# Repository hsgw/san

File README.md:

SAN 
=======================================

3keys macro pad.
- STM32F042F6P6
- kailh hotswap socket (MX compatible switch)
- on-chip usb-DFU bootloader
- QMK Firmware(https://github.com/hsgw/qmk_firmware/tree/san)

## Issues
### Rev.1
- 基板上の`BOOT`と`RESET`のシルクが逆になっている
(正しくは`SW1 RESET`, `SW2 BOOT`)

## ビルドガイド
1. 組立てる前にPCと接続してキーボードとして認識されるか、動作を確認する
(ファームウェアが書かれていない場合はブートローダモードで接続されます)
2. ブートローダへ入ってQMK Firmwareからの書き込みを確認する
https://github.com/hsgw/qmk_firmware/san
3. プレート、スイッチを取り付ける
4. ボトムプレートを取り付ける

## ブートローダモード
### 入り方
1. RESETスイッチを押す
2. BOOTスイッチを押す
3. RESETスイッチを離す
4. BOOTスイッチを離す

### (windowsの場合)ドライバを入れ替える
Zadigを使用してOS標準で入るドライバをWinUSBのものに入れ替える必要があります。
1. zadigをダウンロード、解凍する。(https://zadig.akeo.ie/)
2. キーボードをbootloaderモードでPCに接続する   
(この段階では```STM Device in DFU Mode```として認識されているはず)
3. zadigを起動して```Options → List All devices```にチェック
4. ```STM Device in DFU Mode```もしくは```STM32 BOOTLOADER```を選択して、```WinUSB```をインストールする   
**書き換えるデバイス名を必ず確認してから```Replace Driver```を押して下さい。**   
**間違えたデバイスのドライバを書き換えると最悪PCが操作不能になります**

問い合わせ先
Twitter(https://twitter.com/hsgw)もしくはurkwtky[at]gmail.comまで

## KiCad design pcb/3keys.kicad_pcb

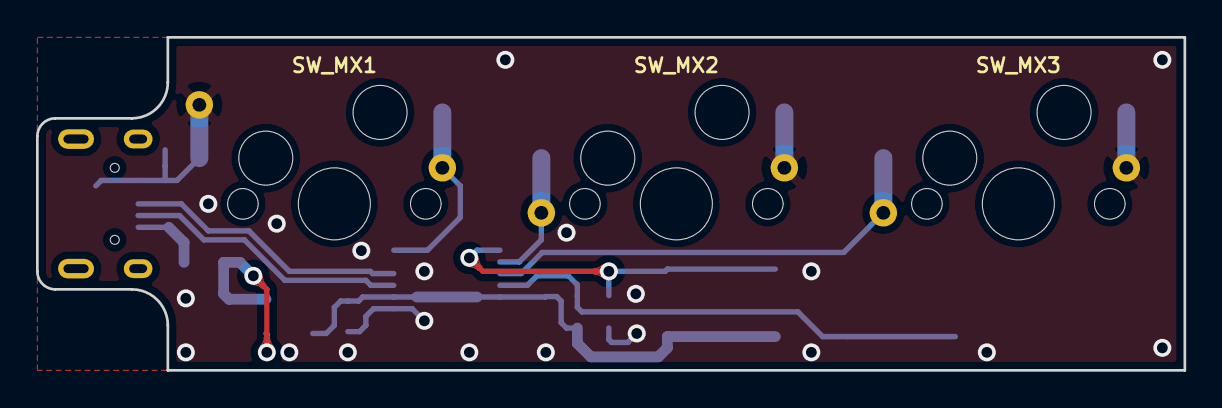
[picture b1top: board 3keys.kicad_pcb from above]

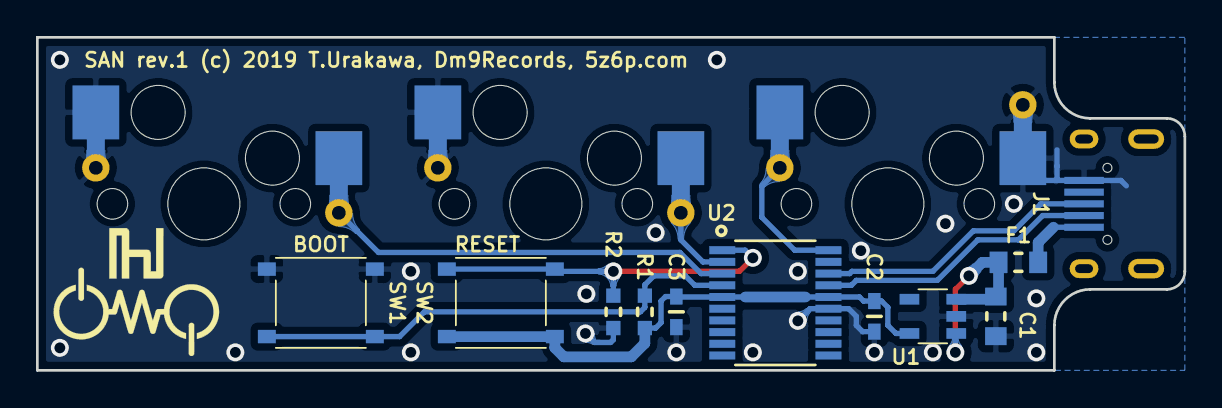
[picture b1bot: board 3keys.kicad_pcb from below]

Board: 2 copper layers, 63.8 x 18.5 mm, 14 parts (11 on the bottom side), 11 nets.

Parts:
C1: 10u; C2012_hand
C2, C3: 0.1u; C1608_Hand
F1: 100mA; C2012_hand
J1: USB_OTG; USB-microB-LCSC-U-F-M5DD-W-2
R1, R2: 10k; R1608_Hand
SW1, SW2: SW_Push; TACT_5.1x5.1
SW_MX1, SW_MX2, SW_MX3: SW_Push; SW_kailh_MX_socket_repairable_small
U1: TLV70012_SOT23-5; SOT-23-5
U2: STM32F042F6Px; TSSOP-20_4.4x6.5mm_Pitch0.65mm

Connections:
+3V3: C2.1, C3.1, R1.1, SW2.1, U1.5, U2.5, U2.16
/SW1: SW_MX1.2, U2.20
/SW2: SW_MX2.1, U2.2
/SW3: SW_MX3.1, U2.3
/USB_D+: J1.3, U2.18
/USB_D-: J1.2, U2.17
GND: C1.2, C2.2, C3.2, J1.5, R2.2, SW1.1, SW_MX1.1, SW_MX2.2, SW_MX3.2, U1.2, U2.15
unnamed: C1.1, F1.1, U1.1, U1.3
unnamed: R1.2, SW1.2, U2.4
unnamed: R2.1, SW2.2, U2.1
VBUS: F1.2, J1.1

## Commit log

2019-08-31 1st commit

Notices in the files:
pcb/3keys.kicad_pcb:
SAN rev.1 (c) 2019 T.Urakawa, Dm9Records, 5z6p.com
